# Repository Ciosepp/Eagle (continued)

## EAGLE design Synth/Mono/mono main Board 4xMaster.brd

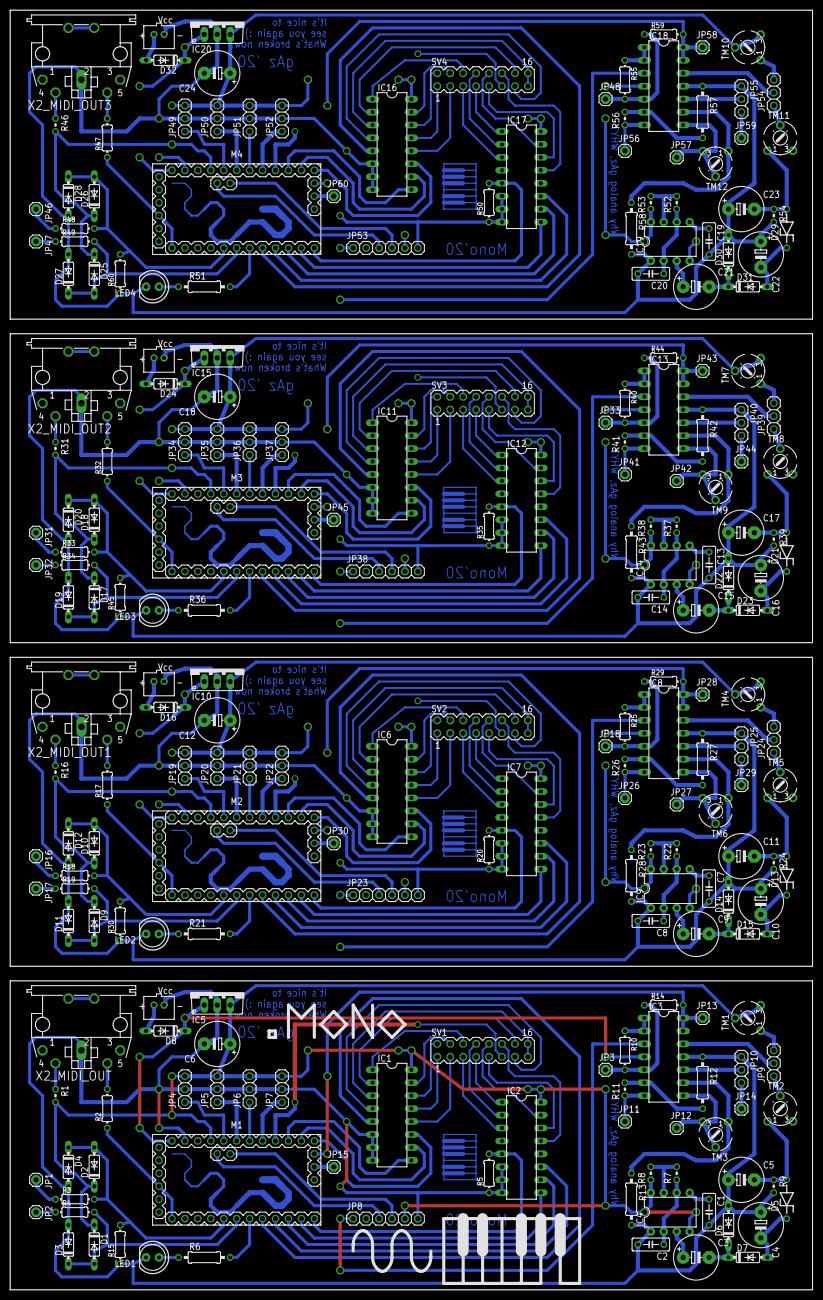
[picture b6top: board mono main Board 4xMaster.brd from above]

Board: 2 copper layers, 157.5 x 251.1 mm, 228 parts (0 on the bottom side), 256 nets.

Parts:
C1, C2, C7, C8, C13, C14, C19, C20: C050-025X075
C3, C4, C5, C6, C9, C10, C11, C12, C15, C16, C17, C18, C21, C22, C23, C24: E5-8,5
CN1, CN2, CN3, CN4: Vcc; JST-PH-2-THM
D1, D2, D3, D4, D7, D9, D10, D11, D12, D15, D17, D18, D19, D20, D23, D25, D26, D27, D28, D31: 1N4148; DO35-7
D5, D13, D21, D29: ZDIO-7.5
D6, D8, D14, D16, D22, D24, D30, D32: 4148; DO35-7
IC1, IC2, IC6, IC7, IC11, IC12, IC16, IC17: 74151N; DIL16
IC3, IC8, IC13, IC18: LM324N; DIL14
IC4, IC9, IC14, IC19: NE555N; DIL08-ROUND
IC5, IC10, IC15, IC20: 7805; TO220V
JP1, JP16, JP31, JP46: CK I/O; 1X01
JP2, JP17, JP32, JP47: GATE; 1X01
JP3, JP18, JP33, JP48: CV; 1X01
JP4, JP19, JP34, JP49: oct_selection; 1X03
JP5, JP20, JP35, JP50: int_ck_rate; 1X03
JP6, JP21, JP36, JP51: ck_div; 1X03
JP7, JP22, JP37, JP52: mode; 1X03
JP8, JP23, JP38, JP53: 1X06
JP9, JP24, JP39, JP54: pitch_bend; 1X03
JP10, JP25, JP40, JP55: expression; 1X03
JP11, JP26, JP41, JP56: CV_Bend; 1X01
JP12, JP27, JP42, JP57: Exp_out; 1X01
JP13, JP28, JP43, JP58: Bend; 1X01
JP14, JP29, JP44, JP59: Exp_IN; 1X01
JP15, JP30, JP45, JP60: Seq; 1X01
LED1, LED2, LED3, LED4: LED5MM
M1, M2, M3, M4: ARDUINO-PRO-MINI-5.0V; ARDUINO-PRO-MINI
R1, R16, R31, R46: 0204V
R2, R10, R14, R17, R25, R29, R32, R40, R44, R47, R55, R59: 0204/7
R3, R18, R33, R48: 330; 0204/7
R4, R19, R34, R49: 300; 0204/7
R5, R20, R35, R50: 10k; 0204/7
R6, R21, R36, R51: 330; 0207/10
R7, R8, R11, R22, R23, R26, R37, R38, R41, R52, R53, R56: 10k; 0204V
R9, R24, R39, R54: 220; 0204V
R12, R13, R27, R28, R42, R43, R57, R58: 10k; 0207/10
R15, R30, R45, R60: 1k; 0204/7
SV1, SV2, SV3, SV4: MA08-2
TM1, TM2, TM3, TM4, TM5, TM6, TM7, TM8, TM9, TM10, TM11, TM12: 6MM
X2_MIDI_OUT, X2_MIDI_OUT1, X2_MIDI_OUT2, X2_MIDI_OUT3: MAB5SH

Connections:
AGND: C1.2, C2.2, C4.+, C5.+, C6.-, CN1.2, D3.A, D4.A, D6.A, IC1.6, IC1.7, IC1.8, IC2.6, IC2.7, IC2.8, IC3.11, IC4.1, IC5.2, JP4.2, JP5.2, JP6.2, JP7.2, JP8.6, JP10.1, LED1.K, M1.J6.2, R5.1, R9.2, R12.1, R13.2, R15.1, X2_MIDI_OUT.2
AGND1: C7.2, C8.2, C10.+, C11.+, C12.-, CN2.2, D11.A, D12.A, D14.A, IC6.6, IC6.7, IC6.8, IC7.6, IC7.7, IC7.8, IC8.11, IC9.1, IC10.2, JP19.2, JP20.2, JP21.2, JP22.2, JP23.6, JP25.1, LED2.K, M2.J6.2, R20.1, R24.2, R27.1, R28.2, R30.1, X2_MIDI_OUT1.2
AGND2: C13.2, C14.2, C16.+, C17.+, C18.-, CN3.2, D19.A, D20.A, D22.A, IC11.6, IC11.7, IC11.8, IC12.6, IC12.7, IC12.8, IC13.11, IC14.1, IC15.2, JP34.2, JP35.2, JP36.2, JP37.2, JP38.6, JP40.1, LED3.K, M3.J6.2, R35.1, R39.2, R42.1, R43.2, R45.1, X2_MIDI_OUT2.2
AGND3: C19.2, C20.2, C22.+, C23.+, C24.-, CN4.2, D27.A, D28.A, D30.A, IC16.6, IC16.7, IC16.8, IC17.6, IC17.7, IC17.8, IC18.11, IC19.1, IC20.2, JP49.2, JP50.2, JP51.2, JP52.2, JP53.6, JP55.1, LED4.K, M4.J6.2, R50.1, R54.2, R57.1, R58.2, R60.1, X2_MIDI_OUT3.2
unnamed: IC1.12, SV1.3
unnamed: IC1.13, SV1.1
unnamed: IC1.14, SV1.2
unnamed: IC1.15, SV1.4
unnamed: IC1.1, SV1.6
unnamed: IC1.4, SV1.13
unnamed: IC1.2, SV1.14
unnamed: IC1.3, SV1.15
unnamed: IC6.11, M2.J6.12
unnamed: IC6.10, M2.J6.11
unnamed: IC2.13, SV1.12
unnamed: IC2.14, SV1.9
unnamed: IC2.15, SV1.10
unnamed: IC2.1, SV1.7
unnamed: IC2.2, SV1.8
unnamed: JP1.1, R3.1
unnamed: IC1.11, M1.J6.12
unnamed: IC1.10, M1.J6.11
unnamed: M1.J7.12, R2.1
unnamed: IC2.3, SV1.5
unnamed: JP8.3, M1.J2.2
unnamed: D2.A, D4.C, M1.J7.8, R3.2, R15.2
unnamed: D1.A, D3.C, M1.J7.7, R4.2
unnamed: IC2.5, M1.J7.1, R5.2
unnamed: IC1.5, M1.J7.5
unnamed: JP6.1, M1.J6.7
unnamed: JP5.1, M1.J6.6
unnamed: JP2.1, R4.1
unnamed: JP8.4, M1.J2.1
unnamed: R2.2, X2_MIDI_OUT.5
unnamed: R1.1, X2_MIDI_OUT.4
unnamed: JP16.1, R18.1
unnamed: IC3.9, R13.1, TM3.A
unnamed: JP4.1, M1.J6.5
unnamed: IC2.9, M1.J7.2
unnamed: IC2.10, M1.J7.3
unnamed: IC2.11, M1.J7.4
unnamed: LED1.A, R6.1
unnamed: M1.J7.6, R6.2
unnamed: IC4.7, R7.2, R8.2
unnamed: C2.1, IC4.2, IC4.6, R7.1
unnamed: C1.1, IC4.5
unnamed: IC3.1, IC3.2, R10.1
unnamed: C3.+, IC4.3
unnamed: C3.-, D6.C, D7.C
unnamed: C4.-, D5.C, D7.A
unnamed: C5.-, D5.A, R9.1, TM2.A
unnamed: IC3.12, JP9.2
unnamed: IC3.13, IC3.14, JP13.1, M1.J3.3, R14.2
unnamed: JP9.3, TM1.A
unnamed: IC3.10, JP10.2
unnamed: IC3.8, JP12.1, TM3.E, TM3.S
unnamed: CN1.1, D8.A
unnamed: JP9.1, TM2.S
unnamed: IC3.6, R11.2, R12.2
unnamed: IC3.7, JP11.1, R11.1
unnamed: D8.C, IC3.4, IC5.1, M1.J6.1
unnamed: IC1.9, M1.J6.10
unnamed: IC3.3, JP8.1
unnamed: IC3.5, JP3.1, R10.2, R14.1
unnamed: JP10.3, JP14.1
unnamed: M1.J6.9, SV1.11
unnamed: D10.A, D12.C, M2.J7.8, R18.2, R30.2
unnamed: D9.A, D11.C, M2.J7.7, R19.2
unnamed: IC7.5, M2.J7.1, R20.2
unnamed: JP17.1, R19.1
unnamed: JP7.1, M1.J6.8
unnamed: JP23.3, M2.J2.2
unnamed: JP23.4, M2.J2.1
unnamed: JP15.1, M1.J3.2
unnamed: R17.2, X2_MIDI_OUT1.5
unnamed: R16.1, X2_MIDI_OUT1.4
unnamed: JP21.1, M2.J6.7
unnamed: JP20.1, M2.J6.6
unnamed: IC7.9, M2.J7.2
unnamed: IC7.10, M2.J7.3
unnamed: IC7.11, M2.J7.4
unnamed: LED2.A, R21.1
unnamed: M2.J7.6, R21.2
unnamed: C8.1, IC9.2, IC9.6, R22.1
unnamed: C7.1, IC9.5
unnamed: IC9.7, R22.2, R23.2
unnamed: C9.+, IC9.3
unnamed: C9.-, D14.C, D15.C
unnamed: C10.-, D13.C, D15.A
unnamed: C11.-, D13.A, R24.1, TM5.A
unnamed: IC8.1, IC8.2, R25.1
unnamed: IC8.12, JP24.2
unnamed: IC8.13, IC8.14, JP28.1, M2.J3.3, R29.2
unnamed: IC8.10, JP25.2
unnamed: IC8.8, JP27.1, TM6.E, TM6.S
unnamed: JP24.1, TM5.S
unnamed: JP24.3, TM4.A
unnamed: IC8.6, R26.2, R27.2
unnamed: IC8.7, JP26.1, R26.1
unnamed: IC8.3, JP23.1
unnamed: CN2.1, D16.A
unnamed: D16.C, IC8.4, IC10.1, M2.J6.1
unnamed: JP19.1, M2.J6.5
unnamed: IC6.9, M2.J6.10
unnamed: M2.J7.12, R17.1
unnamed: IC8.5, JP18.1, R25.2, R29.1
unnamed: JP25.3, JP29.1
unnamed: IC8.9, R28.1, TM6.A
unnamed: IC6.12, SV2.3
unnamed: IC6.13, SV2.1
unnamed: IC6.14, SV2.2
unnamed: IC6.15, SV2.4
unnamed: IC6.1, SV2.6
unnamed: IC6.4, SV2.13
unnamed: IC6.2, SV2.14
unnamed: IC6.3, SV2.15
unnamed: IC7.13, SV2.12
unnamed: IC7.14, SV2.9
unnamed: IC7.15, SV2.10
unnamed: IC7.1, SV2.7
unnamed: IC7.2, SV2.8
unnamed: IC7.3, SV2.5
unnamed: M2.J6.9, SV2.11
unnamed: JP22.1, M2.J6.8
unnamed: IC6.5, M2.J7.5
unnamed: JP30.1, M2.J3.2
unnamed: IC11.11, M3.J6.12
unnamed: IC11.10, M3.J6.11
unnamed: JP31.1, R33.1
unnamed: D18.A, D20.C, M3.J7.8, R33.2, R45.2
unnamed: D17.A, D19.C, M3.J7.7, R34.2
unnamed: IC12.5, M3.J7.1, R35.2
unnamed: JP32.1, R34.1
unnamed: JP38.3, M3.J2.2
unnamed: JP38.4, M3.J2.1
unnamed: R32.2, X2_MIDI_OUT2.5
unnamed: R31.1, X2_MIDI_OUT2.4
unnamed: JP36.1, M3.J6.7
unnamed: JP35.1, M3.J6.6
unnamed: IC12.9, M3.J7.2
unnamed: IC12.10, M3.J7.3
unnamed: IC12.11, M3.J7.4
unnamed: LED3.A, R36.1
unnamed: M3.J7.6, R36.2
unnamed: C14.1, IC14.2, IC14.6, R37.1
unnamed: C13.1, IC14.5
unnamed: IC14.7, R37.2, R38.2
unnamed: C15.+, IC14.3
unnamed: C15.-, D22.C, D23.C
unnamed: C16.-, D21.C, D23.A
unnamed: C17.-, D21.A, R39.1, TM8.A
unnamed: IC13.1, IC13.2, R40.1
unnamed: IC13.12, JP39.2
unnamed: IC13.13, IC13.14, JP43.1, M3.J3.3, R44.2
unnamed: IC13.10, JP40.2
unnamed: IC13.8, JP42.1, TM9.E, TM9.S
unnamed: JP39.1, TM8.S
unnamed: JP39.3, TM7.A
unnamed: IC13.6, R41.2, R42.2
unnamed: IC13.7, JP41.1, R41.1
unnamed: IC13.3, JP38.1
unnamed: CN3.1, D24.A
unnamed: D24.C, IC13.4, IC15.1, M3.J6.1
unnamed: JP34.1, M3.J6.5
unnamed: IC11.9, M3.J6.10
unnamed: M3.J7.12, R32.1
unnamed: IC13.5, JP33.1, R40.2, R44.1
unnamed: JP40.3, JP44.1
unnamed: IC13.9, R43.1, TM9.A
unnamed: IC11.12, SV3.3
unnamed: IC11.13, SV3.1
unnamed: IC11.14, SV3.2
unnamed: IC11.15, SV3.4
unnamed: IC11.1, SV3.6
unnamed: IC11.4, SV3.13
unnamed: IC11.2, SV3.14
unnamed: IC11.3, SV3.15
unnamed: IC12.13, SV3.12
unnamed: IC12.14, SV3.9
unnamed: IC12.15, SV3.10
unnamed: IC12.1, SV3.7
unnamed: IC12.2, SV3.8
unnamed: IC12.3, SV3.5
unnamed: M3.J6.9, SV3.11
unnamed: JP37.1, M3.J6.8
unnamed: IC11.5, M3.J7.5
unnamed: JP45.1, M3.J3.2
unnamed: IC16.11, M4.J6.12
unnamed: IC16.10, M4.J6.11
unnamed: JP46.1, R48.1
unnamed: D26.A, D28.C, M4.J7.8, R48.2, R60.2
unnamed: D25.A, D27.C, M4.J7.7, R49.2
unnamed: IC17.5, M4.J7.1, R50.2
unnamed: JP47.1, R49.1
unnamed: JP53.3, M4.J2.2
unnamed: JP53.4, M4.J2.1
unnamed: R47.2, X2_MIDI_OUT3.5
unnamed: R46.1, X2_MIDI_OUT3.4
unnamed: JP51.1, M4.J6.7
unnamed: JP50.1, M4.J6.6
unnamed: IC17.9, M4.J7.2
unnamed: IC17.10, M4.J7.3
unnamed: IC17.11, M4.J7.4
unnamed: LED4.A, R51.1
unnamed: M4.J7.6, R51.2
unnamed: C20.1, IC19.2, IC19.6, R52.1
unnamed: C19.1, IC19.5
unnamed: IC19.7, R52.2, R53.2
unnamed: C21.+, IC19.3
unnamed: C21.-, D30.C, D31.C
unnamed: C22.-, D29.C, D31.A
unnamed: C23.-, D29.A, R54.1, TM11.A
unnamed: IC18.1, IC18.2, R55.1
unnamed: IC18.12, JP54.2
unnamed: IC18.13, IC18.14, JP58.1, M4.J3.3, R59.2
unnamed: IC18.10, JP55.2
unnamed: IC18.8, JP57.1, TM12.E, TM12.S
unnamed: JP54.1, TM11.S
unnamed: JP54.3, TM10.A
unnamed: IC18.6, R56.2, R57.2
unnamed: IC18.7, JP56.1, R56.1
unnamed: IC18.3, JP53.1
unnamed: CN4.1, D32.A
unnamed: D32.C, IC18.4, IC20.1, M4.J6.1
unnamed: JP49.1, M4.J6.5
unnamed: IC16.9, M4.J6.10
unnamed: M4.J7.12, R47.1
unnamed: IC18.5, JP48.1, R55.2, R59.1
unnamed: JP55.3, JP59.1
unnamed: IC18.9, R58.1, TM12.A
unnamed: IC16.12, SV4.3
unnamed: IC16.13, SV4.1
unnamed: IC16.14, SV4.2
unnamed: IC16.15, SV4.4
unnamed: IC16.1, SV4.6
unnamed: IC16.4, SV4.13
unnamed: IC16.2, SV4.14
unnamed: IC16.3, SV4.15
unnamed: IC17.13, SV4.12
unnamed: IC17.14, SV4.9
unnamed: IC17.15, SV4.10
unnamed: IC17.1, SV4.7
unnamed: IC17.2, SV4.8
unnamed: IC17.3, SV4.5
unnamed: M4.J6.9, SV4.11
unnamed: JP52.1, M4.J6.8
unnamed: IC16.5, M4.J7.5
unnamed: JP60.1, M4.J3.2
PE: X2_MIDI_OUT.PE, X2_MIDI_OUT.PE@
PE1: X2_MIDI_OUT1.PE, X2_MIDI_OUT1.PE@
PE2: X2_MIDI_OUT2.PE, X2_MIDI_OUT2.PE@
PE3: X2_MIDI_OUT3.PE, X2_MIDI_OUT3.PE@
VCC: C6.+, D1.C, D2.C, IC1.16, IC2.16, IC4.4, IC4.8, IC5.3, JP4.3, JP5.3, JP6.3, JP7.3, JP8.5, M1.J6.4, R1.2, R8.1, TM1.E, TM1.S
VCC1: C12.+, D9.C, D10.C, IC6.16, IC7.16, IC9.4, IC9.8, IC10.3, JP19.3, JP20.3, JP21.3, JP22.3, JP23.5, M2.J6.4, R16.2, R23.1, TM4.E, TM4.S
VCC2: C18.+, D17.C, D18.C, IC11.16, IC12.16, IC14.4, IC14.8, IC15.3, JP34.3, JP35.3, JP36.3, JP37.3, JP38.5, M3.J6.4, R31.2, R38.1, TM7.E, TM7.S
VCC3: C24.+, D25.C, D26.C, IC16.16, IC17.16, IC19.4, IC19.8, IC20.3, JP49.3, JP50.3, JP51.3, JP52.3, JP53.5, M4.J6.4, R46.2, R53.1, TM10.E, TM10.S
